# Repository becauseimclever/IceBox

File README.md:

# IceBox
Stickless Fight stick controller

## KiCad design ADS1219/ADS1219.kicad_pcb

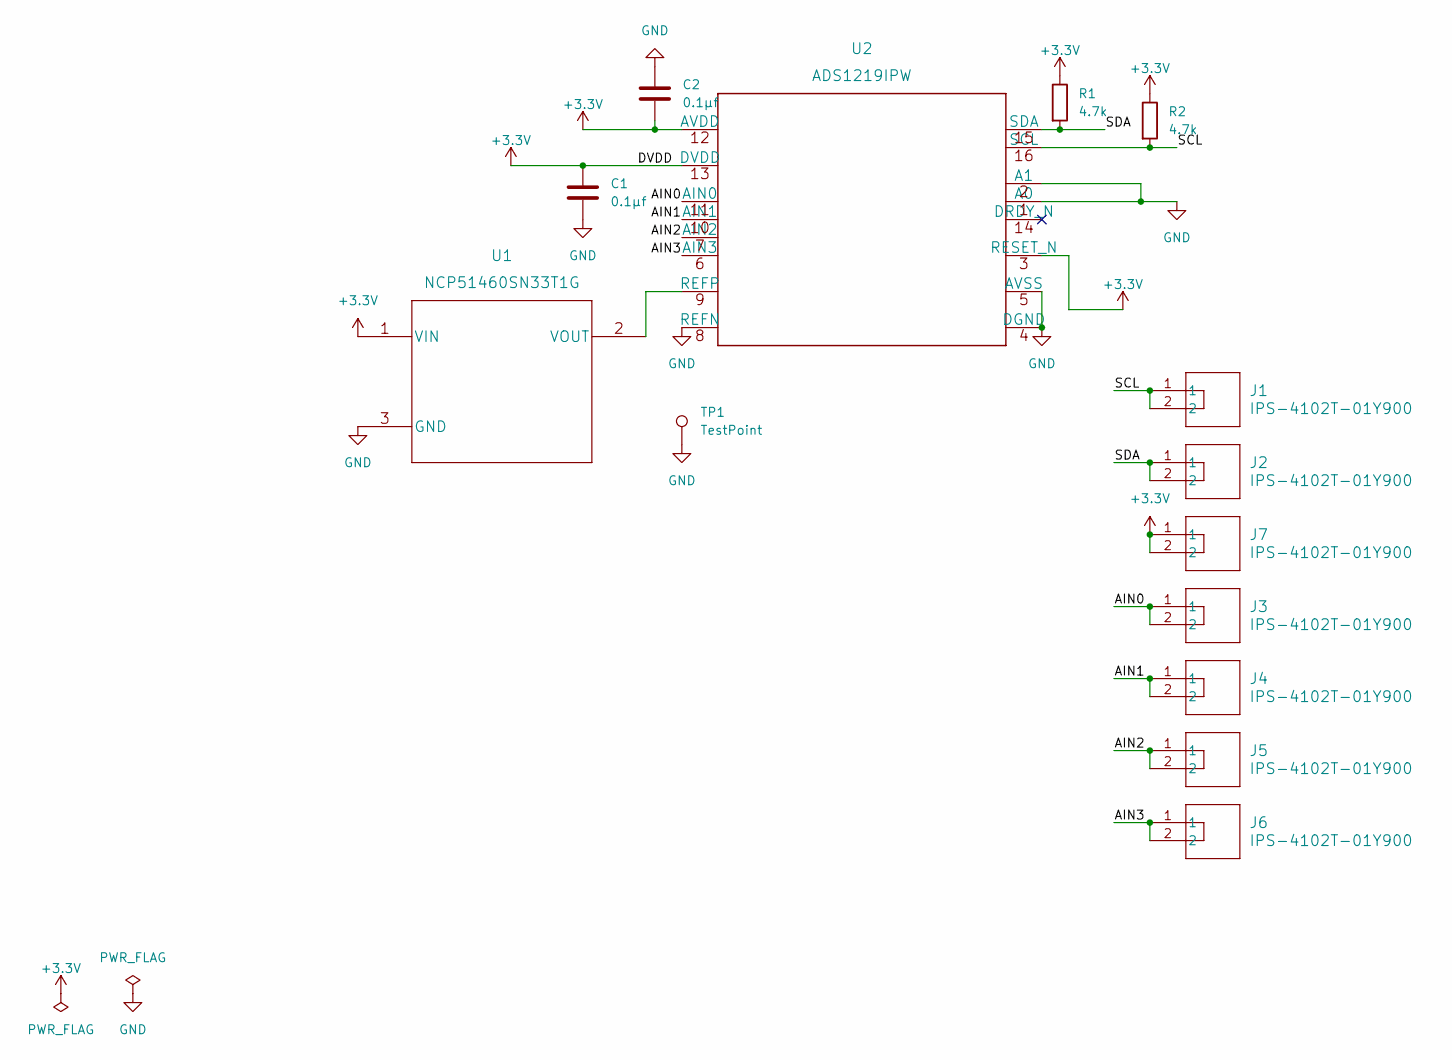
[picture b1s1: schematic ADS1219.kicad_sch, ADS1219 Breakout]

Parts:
C1, C2: 0.1μf; C_0805_2012Metric_Pad1.18x1.45mm_HandSolder
J1, J2, J3, J4, J5, J6, J7: IPS-4102T-01Y900; CONN2_IPS-4102T_IRE
R1, R2: 4.7k; R_0805_2012Metric_Pad1.20x1.40mm_HandSolder
TP1: TestPoint; TestPoint_Pad_D4.0mm
U1: NCP51460SN33T1G
U2: ADS1219IPW

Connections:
+3.3V: C1.2, C2.1, J7.1, J7.2, R1.1, R2.1, U1.1 (VIN), U2.3 (RESET_N), U2.12 (AVDD), U2.13 (DVDD)
/AIN0: J3.1, J3.2, U2.11 (AIN0)
/AIN1: J4.1, J4.2, U2.10 (AIN1)
/AIN2: J5.1, J5.2, U2.7 (AIN2)
/AIN3: J6.1, J6.2, U2.6 (AIN3)
/SCL: J1.1, J1.2, R2.2, U2.16 (SCL)
/SDA: J2.1, J2.2, R1.2, U2.15 (SDA)
GND: C1.1, C2.2, TP1.1, U1.3 (GND), U2.1 (A0), U2.2 (A1), U2.4 (DGND), U2.5 (AVSS), U2.8 (REFN)
unnamed: U1.2 (VOUT), U2.9 (REFP)

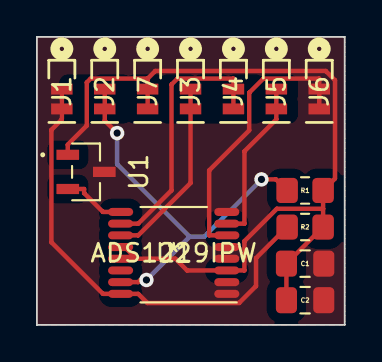
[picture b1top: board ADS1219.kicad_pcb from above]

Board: 2 copper layers, 17.1 x 16.0 mm, 14 parts (1 on the bottom side), 9 nets.

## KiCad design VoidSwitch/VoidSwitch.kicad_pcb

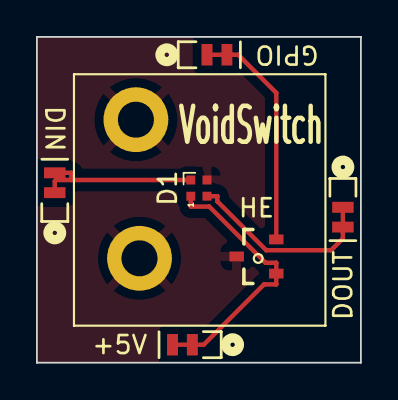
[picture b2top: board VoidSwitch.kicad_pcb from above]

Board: 2 copper layers, 18.0 x 18.1 mm, 8 parts (1 on the bottom side), 5 nets.

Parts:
+5V: IPS-4102T-01Y900; CONN2_IPS-4102T_IRE
AM0:1: VoidSwitch; VoidSwitch_1u_SMD
D1: WS2812B; LED_SK6812_EC15_1.5x1.5mm
DIN: IPS-4102T-01Y900; CONN2_IPS-4102T_IRE
DOUT: IPS-4102T-01Y900; CONN2_IPS-4102T_IRE
GND: TestPoint; TestPoint_Loop_D3.80mm_Drill2.0mm
GPIO: IPS-4102T-01Y900; CONN2_IPS-4102T_IRE
HE: DRV5032FBDBZR; DBZ0003A_L

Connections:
+5V: +5V.1, +5V.2, D1.1 (VDD), HE.1 (VCC)
/DIN: D1.4 (DIN), DIN.1, DIN.2
/DOUT: D1.2 (DOUT), DOUT.1, DOUT.2
/GPIO: GPIO.1, GPIO.2, HE.2 (OUT)
GND: D1.3 (VSS), GND.1, HE.3 (GND)

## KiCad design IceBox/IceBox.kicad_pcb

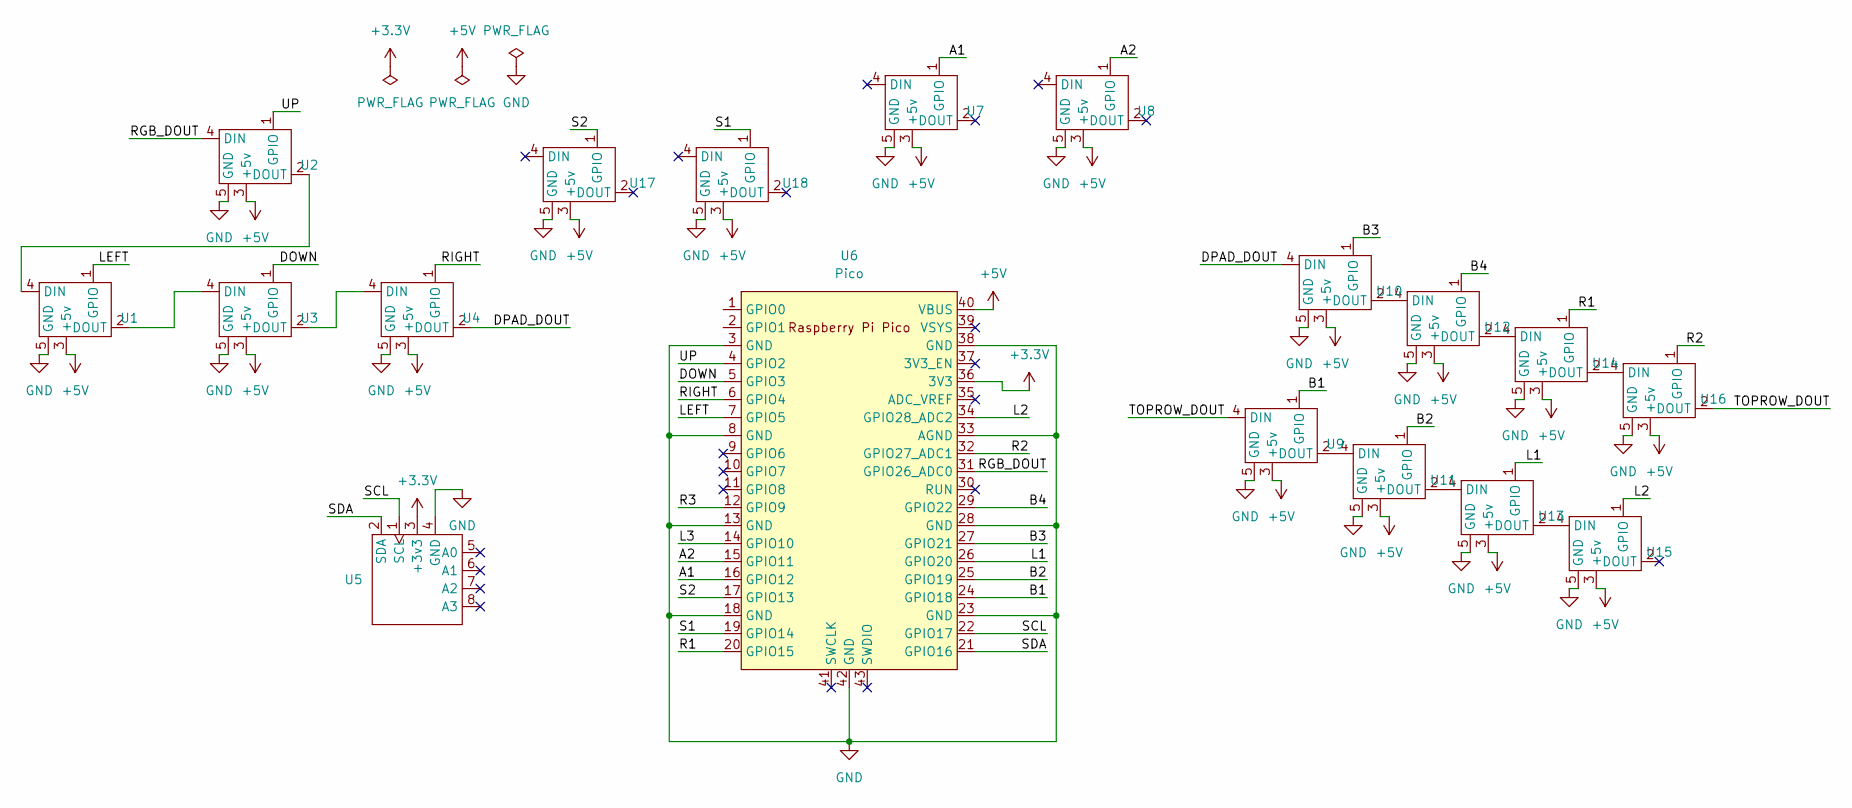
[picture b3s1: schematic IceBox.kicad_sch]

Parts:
U1, U2, U3, U4, U7, U8, U9, U10, U11, U12, U13, U14, U15, U16, U17, U18: voidswitch_1
U5: ADC
U6: Pico; RPi_Pico_SMD_TH_1

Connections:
+3.3V: U5.3 (+3v3), U6.36 (3V3)
+5V: U1.3 (+5v), U2.3 (+5v), U3.3 (+5v), U4.3 (+5v), U6.40 (VBUS), U7.3 (+5v), U8.3 (+5v), U9.3 (+5v), U10.3 (+5v), U11.3 (+5v), U12.3 (+5v), U13.3 (+5v), U14.3 (+5v), U15.3 (+5v), U16.3 (+5v), U17.3 (+5v), U18.3 (+5v)
/A1: U6.16 (GPIO12), U7.1 (GPIO)
/A2: U6.15 (GPIO11), U8.1 (GPIO)
/B1: U6.24 (GPIO18), U9.1 (GPIO)
/B2: U6.25 (GPIO19), U11.1 (GPIO)
/B3: U6.27 (GPIO21), U10.1 (GPIO)
/B4: U6.29 (GPIO22), U12.1 (GPIO)
/DOWN: U3.1 (GPIO), U6.5 (GPIO3)
/DPAD_DOUT: U4.2 (DOUT), U10.4 (DIN)
/L1: U6.26 (GPIO20), U13.1 (GPIO)
/L2: U6.34 (GPIO28_ADC2), U15.1 (GPIO)
/L3: U6.14 (GPIO10)
/LEFT: U1.1 (GPIO), U6.7 (GPIO5)
/R1: U6.20 (GPIO15), U14.1 (GPIO)
/R2: U6.32 (GPIO27_ADC1), U16.1 (GPIO)
/R3: U6.12 (GPIO9)
/RGB_DOUT: U2.4 (DIN), U6.31 (GPIO26_ADC0)
/RIGHT: U4.1 (GPIO), U6.6 (GPIO4)
/S1: U6.19 (GPIO14), U18.1 (GPIO)
/S2: U6.17 (GPIO13), U17.1 (GPIO)
/SCL: U5.1 (SCL), U6.22 (GPIO17)
/SDA: U5.2 (SDA), U6.21 (GPIO16)
/TOPROW_DOUT: U9.4 (DIN), U16.2 (DOUT)
/UP: U2.1 (GPIO), U6.4 (GPIO2)
GND: U1.5 (GND), U2.5 (GND), U3.5 (GND), U4.5 (GND), U5.4 (GND), U6.3 (GND), U6.8 (GND), U6.13 (GND), U6.18 (GND), U6.23 (GND), U6.28 (GND), U6.33 (AGND), U6.38 (GND), U6.42 (GND), U7.5 (GND), U8.5 (GND), U9.5 (GND), U10.5 (GND), U11.5 (GND), U12.5 (GND), U13.5 (GND), U14.5 (GND), U15.5 (GND), U16.5 (GND), U17.5 (GND), U18.5 (GND)
unnamed: U1.4 (DIN), U2.2 (DOUT)
unnamed: U1.2 (DOUT), U3.4 (DIN)
unnamed: U3.2 (DOUT), U4.4 (DIN)
unnamed: U10.2 (DOUT), U12.4 (DIN)
unnamed: U9.2 (DOUT), U11.4 (DIN)
unnamed: U11.2 (DOUT), U13.4 (DIN)
unnamed: U12.2 (DOUT), U14.4 (DIN)
unnamed: U13.2 (DOUT), U15.4 (DIN)
unnamed: U14.2 (DOUT), U16.4 (DIN)

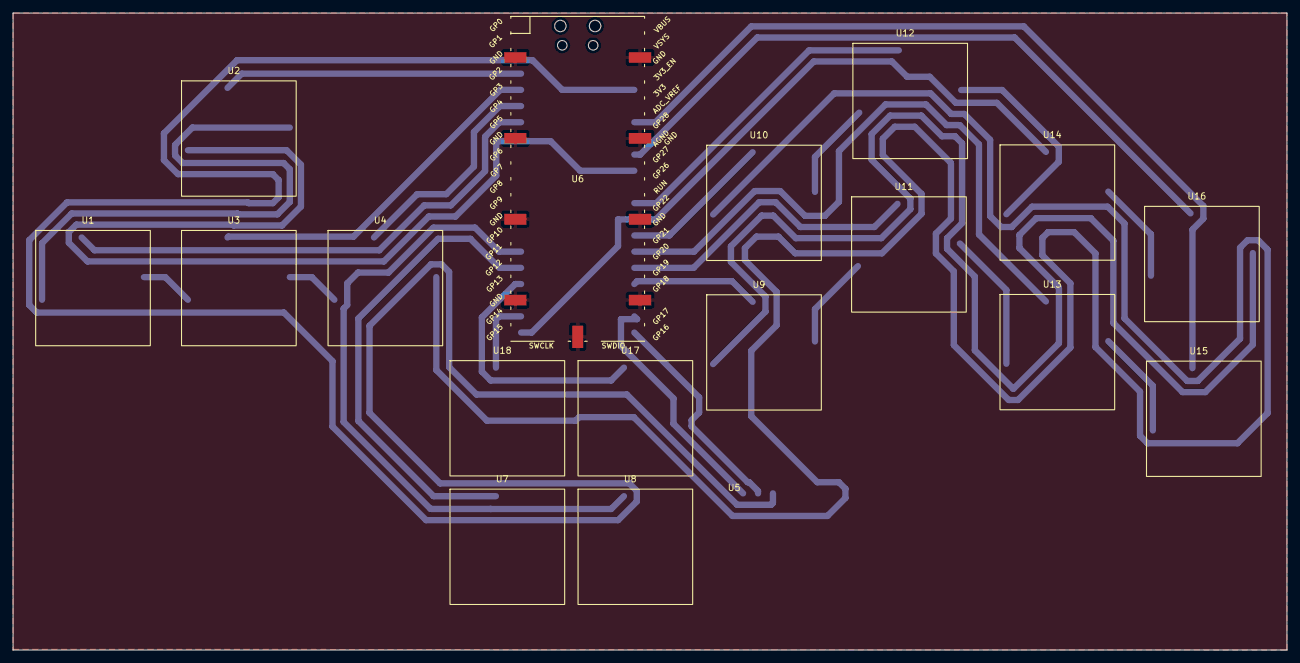
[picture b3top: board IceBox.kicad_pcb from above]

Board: 2 copper layers, 200.0 x 100.0 mm, 18 parts (0 on the bottom side), 33 nets.

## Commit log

2023-06-15 getting setup
2023-07-03 syncing

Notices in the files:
parts and their libraries:
Copyright 2021 Accelerated Designs. All rights reserved.
